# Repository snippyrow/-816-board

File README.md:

# Retro computer board!

A retro computer motherboard for the W65C816S CPU.
Dual-core expandable, 16mb extended memory, four expansion ports.

## *WHY* did I make this??
I have always loved building things with my hands, especially electronics things. I also love computers, and always to learn how they work. I believe that this is part of that hobby, building myself a computer system to play around with. I want to develop software, as well as expandable hardware. My end goal is to write a complete opertaing system for this build, and have it run DOOM!

# Basic Specifications
The primary core is a W65C816S microcontroller, with 32kb of SRAM. EEPROM Space is only accessible to the primary controller. Each core has its own cache, or SRAM chip. Located in the upper-half of the first page, each is 32kb. If the primary controller wants to access EEPROM, I.E. to copy data to another portion of memory, it only needs to access the lower-half. If the primary wants to access the secondary core cache, it uses the expanded memory space. There are two types of busses: core-only and global. The global bus is arbitrated between the two cores. The primary gets priority, then the secondary. In order for the first to access secondary, it must first disable the secondary core. This allows it to always be able to write. The primary core must not access the secondary core too often, as it must be disabled beforehand. If the secondary core needs to access the main bus, it queues to wait before the primary CPU does an internal cycle. At that moment it will take whatever is in the queue registers. This means that the secondary must not access the main memory too often. The secondary cache is only exposed to the global bus if the primary is using it for a transfer. 

The system is powerful enough to run a basic operating system, and provides options to expand into a workable computer system.

## Advanced
The system uses two cores, the W65C816S core. It is not a drop-in replacement for the W65C02S, and samples data during the falling edge of the PHI2. Each core starts in a 6502-emulation mode, and then transitions to the native '816 mode. Each core can access up to 16MB of memory and has 16-bit internal registers. The primary core contains 32kb of EEPROM space as well as 32kb of SRAM space. The secondary core is disabled at runtime, and must be re-enabled later. The low 65kb of the memory (2^16 bytes worth) are used to communicate and run simple programs. The 32kb space acts as a sort of cache system for each core, and they can communicate largely based on the upper shared memory. Beyond the low 65kb there are devices and expansion memory. The secondary core is unable to reach the primary core, though the primary core can access the secondary core by an expansion device. The first devices after the local memory are the expansion devices. Not only are the expansion ports physically on the board mapped here, but so is the control register for the secondary core, as well as the built-in serial port controller. 

While the primary core is not actively using the global/shared memory, the secondary core is free to do so. To upload a program or start a second process, the secondary core must first be disabled and reset. Then, the cache is accessed and the program is copied. The reset vector will point to some location in the cache, and it will be re-enabled. **Do not set the reset vector elsewhere.**
As stated previously, when the secondary core needs to access shared memory, whether that be an expansion device or general memory, it latches the address. If reading, it sets a control bit and waits for a NMIB. If writing, it sets the control but the other way and latches the write data. When the write is completed, I.E. once the primary is not active, a NMIB signal is sent signaling that the memory transaction was completed. The WAI (wait for interrupt) can be used. 
The system is based off an expanion-type model, where it encourages expansion devices to be built and used. Some examples could be a VGA card, sound card, or a keyboard/mouse system.

## Primary core operation
The core is initiated during a power-on reset phase. The secondary core is disabled during this time, and no secondary transactions are happening. The primary will disable the built-in serial port built in directly to the secondary, and can work without using the secondary core at all. It can use the global bus like the internal core bus.

## Secondary core operation
There are two bits that control the secondary core: ENABLE (0) and RESET (1). The ENABLE bit is used to turn the core on or of. It uses the RDY pin to do this. Enabling this also allows the queue to begin transferring data. The IRQB pin is used for the serial adapter, and the NMIB is used when an external read request has been completed. The RESET pin is used to control the RESB pin on the secondary, to reset it to a known state. It is recommended to disable the core using the ENABLE bit before changing data on the secondary cache. When the primary CPU goes into an internal cycle, it takes whatever value is in the address latches and will attempt a memory transaction. The only accessible area for the secondary is the expansion planes and the expanded memory lanes. The RWB bit will control whether it is reading or writing. Since this all takes a single cycle, timing does not matter. The secondary should not attempt frequent external writes due to speed limitations. The secondary only has access to up to half the expandable memory space, as the last bit is used internally for deciding whether it is reading the MMU register. A NMI also happens after a write, to tell the core that the write succeeded before overwriting the register again.

## Built-in serial adapter
The built-in serial adapter is wired directly to the secondary core IRQB pin. If it should be disabled, it can be done so by accessing the internal registers. It uses the R6551 chip. Does not include RS232. When reading data from the serial port, it must use the R6551 as an expansion device, located in the external memory lane. This is so that it can be externally controlled by the primary core. Attempt to read by accessing the global data bus, and wait for an interrupt on the NMIB pin. WAI can be used. The same goes for sending data.
The secondary should rely in the WAI instruction to manage external reads and writes, but could also be triggered by an IRQB signal from the serial adapter. Internal control should be programmed to prevent this. NMI has priority, after that an IRQB will be sent. The flow should be as follows: first an IRQB signal is sent, then an attempt to read the device will be followed by a NMIB signal. When a NMIB is sent during the IRQB routine, it will cause a nested interrupt to occur, allowing it to service properly. 

# Timing Control
Timing control is critical for this system. When PHI2 (the clock) goes from high to low, it indicated the start of a new cycle. VDA/VPA pins change about half-way during the PHI2 low period, and indicate whether the CPU is undergoing an internal cycle. Write and read cycles are all sampled on the falling edge. When VDA/VPA update shortly after the falling edge, the primary core is disconnected from the global bus, and it prepares to do a transaction by updating the address that was latched before. write data is also placed onto the data bus if necessary. On the next falling edge, data is written or data is read. If read, it then sends a NMI to tell the core that it read the data. From there it will read the data back from a specific register. When using it to read, it does not exactly read directly from the memory devices. Instead, it reads from a memory management unit that waits for the primary core to open. The secondary can read the MMU register, located in the upper half of the expandable memory space (bit 23). In order to disconnect the primary, BE is set high, disconnecting the data and address busses. Afterwards, the latches are turned on. 
Immediately after the bank address is pushed to the data bus, all read data begins to enter through either the cache space or the shared memory space. RDY is toggled by the control of the first bit in the control register, and is only sampled and updated on the following falling edge of the PHI2.

## Examples
If the primary wants to upload something to the secondary, I.E. change the task, it will first disable the core and push it into a reset. This prevent erroneous memory accesses. Then, with the cache mapped as an expansion memory device, begins accessing. The primary is **blocked** from accessing the secondary cache if the core is active. The only way for the two to communicate is through the shared global memory tables. After it is completed, re-enable the secondary.

# Expansion Ports
The machine contains four expansion ports, wired directly to the primary. Two of the slots are larger, and each one of the two is either wired to IRQB or NMIB. The other two are simply expansion devices. The larger ones have A0-A3, and the smaller ones have A0-A1 as register addresses. The shared memory on the global bus is beyond the 65K from the two cores.
The controller for the secondary, the controller for the serial port, and just about everything else is connected in through the expansion device encoder to save on space.

# Physical Board Explaination
### Primary Core
The primary core uses the W65C816S, with a 24-bit address bus and an 8-bit data bus. The highest byte of the address bus (A16-A23) is pushed onto the data bus during the low phase of PHI2, and is latched at the rising edge of the clock. The address bus comes stable around the same time. During these times, all the chips may stabilize into selecting the correct hardware for the write. Each core has a 74HC373 and a 74HC245 to moderate the data bus and the banked address busses. The BE pin will set the data bus, address bus and RWB pins to high-Z. The banked address byte is fed into a chip that detects if it is anything >0x00. This means that an external cycle is being attempted. If not, the selection uses A15 to select from either RAM or ROM to read/write from. In an external cycle, the primary is shut off from the rest of the device. During an external cycle, the full address is passed to the global address bus, and the data is either passed through from the data bus directly or read in through an octal buffer. The RWB pin is multiplexed along with the secondary.
The expansion slots are wired directly into the primary core NMIB/IRQB pins, and are pulled high on the board. 

### Secondary Core
The secondary core has much the same setup as the primary core, but has some key differences. It can work independently of the primary through its own cache, but lacks an EEPROM space. In order to perform an external read/write, when it detects an external memory transaction it always writes to a large set of registers. These registers latch A0-A22, as well as whether it wants to read or write. It may not be necessary for it to use the full 16MB address space. The secondary cache lies outside of the range that the secondary can reach. When it is latched, it also sets a D-flipflop into a HIGH state. The state of the first flip-flop is transferred over to the external memory device selector, which can choose which device to enable. It is only active during either an external cycle made by the primary or the secondary waiting to write/read data. Now that the devices have a stable address, when an external cycle happens, it sets the second flip-flop into a HIGH state. This will immediately reset both back to LOW, but sends a NMI to the secondary processor.
During an external cycle, the secondary processor latches are always pushed out to the global bus, as well as any data. If no core is desiring to read from the global data bus, then it may go floating. If the secondary desired to write previously, that old data would be pushed, otherwise nothing holds on to the data bus. Therefore the global data bus is always pulled LOW.
A15 is always pulled LOW, and in order to *read* data coming from the global busses, any address from 0x0000-0x7FFF will work. It simply takes the place of the EEPROM space. On the secondary the cache is in the upper half rather than lower.
The secondary processor has two control bits, ENABLE and RESET. ENABLE will control the processor state, pausing it and disabling the address/data busses. The RESET bit will cause it to reset back to a known state. The secondary processor will have all of its data and address busses disabled during this time. The cache can be accessed by the primary core processor during this time, while it is disabled. *It cannot access while running.* While the address and data busses are in a High-Z state, the cache can be selected as an expansion device, and the address/data/RWB for the primary processor are pushed in. The secondary local data bus are always pulled LOW. The secondary address bus is always matches the primary address bus while not enabled, as a way to drive it.

#### Serial adapter
As mentioned earlier, the serial adapter is wired directly to the secondary core, and works as any other expansion device would. The secondary should either disable the adapter or mask interrupts if it were to be doing something other than serial work.

#### Memory selector
The memory selector works entirely off the global address busses for selection, choosing serial devices or memory expansion cards. Devices are only selected if either there is an external cycle or the secondary is waiting to write data. 

# Datasheets
https://www.westerndesigncenter.com/wdc/documentation/w65c816s.pdf

# BOM
| Item               | Quantity | Price (USD) |
|--------------------|----------|-------------|
| JLCPCB 180x140mm | 5 | $25.15 |
| 10K Resistor       | 10       | $1.85       |
| SN74HC373N Latch   | 10       | $9.77       |
| W65C816S6PG-14 MPU | 2        | $24.20      |
| L78L33 Regulator   | 5        | $1.40       |
| 10uF Capacitor     | 5        | $1.15       |
| LED (Red)          | 10       | $2.60       |
| SN74HC04N Inverter | 5        | $6.55       |
| SN74HC21N Gate     | 4        | $2.60       |
| Tactile Switch     | 5        | $1.50       |
| SN74HC245N Transceiver | 10    | $6.22       |
| AT28C256 EEPROM    | 1        | $11.62      |
| 150Ω Resistor      | 4        | $1.44       |
| AS6C62256 SRAM     | 2        | $9.50       |
| 1MΩ Resistor       | 4        | $1.44       |
| SN74HC138N Decoder | 5        | $5.50       |
| 1N914 Diode        | 5        | $0.50       |
| SN74HC10N Gate     | 4        | $2.52       |
| 10kΩ Resistor      | 20       | $0.30       |
| 1kΩ Resistor       | 10       | $0.27       |
| SN74HC32N Gate     | 4        | $2.20       |
| SN74HC688N Comparator | 6     | $8.52       |
| 4.7kΩ Resistor     | 10       | $0.47       |
| SN74HC126N Buffer  | 4        | $2.64       |
| SN74HC00N Gate     | 5        | $3.00       |
| 2N3904 Transistor  | 10       | $0.77       |
| 30pF Capacitor     | 10       | $1.18       |
| 0.1uF Capacitor    | 100      | $4.00       |
| 1MHz Oscillator    | 2        | $6.90       |
| SN74HC08N Gate     | 4        | $2.40       |
| SN74HC74N Flip Flop| 4        | $3.60       |
| 20-pin Socket      | 24       | $3.10       |
| 16-pin Socket      | 20       | $2.42       |
| 14-pin Socket      | 20       | $2.20       |
| 28-pin Socket      | 6        | $3.84       |
| 40-pin Socket      | 4        | $3.68       |

**Total: $167.00**

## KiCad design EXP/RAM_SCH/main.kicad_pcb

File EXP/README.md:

# Custom computer expansion cards!

A collection of expansion cards I plan to build for my custom dual-core W65C816S motherboard. Two examples include: a basic text-based graphics card, and some 2MB RAM modules.

## Why Did I Build These?
A computer without a graphical display, or RAM sticks is pretty useless. You can run some basic algorithms, but that's about it. These pieces of customized hardware will *drastically* improve that this build can do. For more information, please see the parent directory for the main build.

# About
# If you want to see specifics for each expansion card I plan to build, see the directories listed here in this folder.

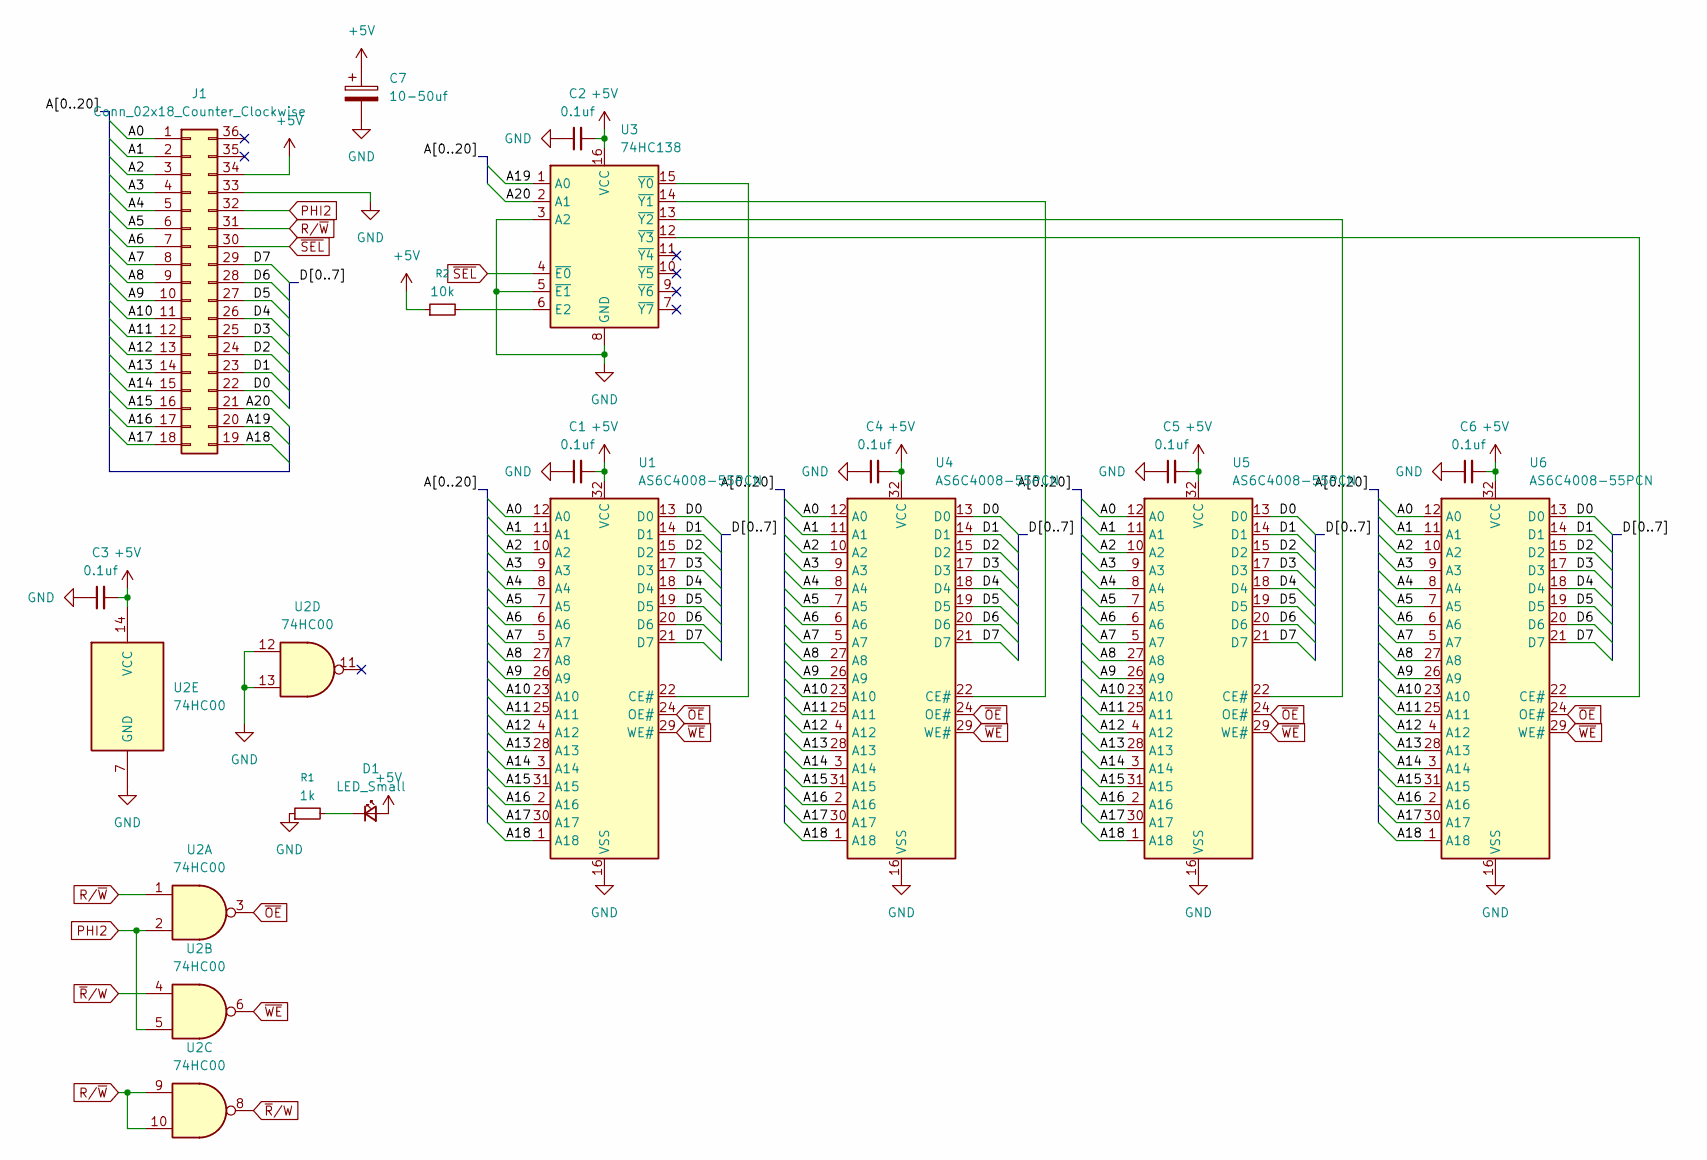
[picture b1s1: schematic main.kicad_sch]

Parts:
C1, C2, C3, C4, C5, C6: 0.1uf; C_Disc_D5.0mm_W2.5mm_P5.00mm
C7: 10-50uf; CP_Radial_D6.3mm_P2.50mm
D1: LED_Small; LED_D3.0mm
J1: Conn_02x18_Counter_Clockwise; AliExpress_36Edge
R1: 1k; R_Axial_DIN0204_L3.6mm_D1.6mm_P5.08mm_Horizontal
R2: 10k; R_Axial_DIN0204_L3.6mm_D1.6mm_P5.08mm_Horizontal
U1, U4, U5, U6: AS6C4008-55PCN; DIP-32_W15.24mm
U2: 74HC00; DIP-14_W7.62mm_Socket
U3: 74HC138; DIP-16_W7.62mm_Socket

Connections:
+5V: C1.2, C2.2, C3.2, C4.2, C5.2, C6.2, C7.1, D1.2 (A), J1.34, R2.1, U1.32 (VCC), U2.14 (VCC), U3.16 (VCC), U4.32 (VCC), U5.32 (VCC), U6.32 (VCC)
/A0: J1.1, U1.12 (A0), U4.12 (A0), U5.12 (A0), U6.12 (A0)
/A1: J1.2, U1.11 (A1), U4.11 (A1), U5.11 (A1), U6.11 (A1)
/A2: J1.3, U1.10 (A2), U4.10 (A2), U5.10 (A2), U6.10 (A2)
/A3: J1.4, U1.9 (A3), U4.9 (A3), U5.9 (A3), U6.9 (A3)
/A4: J1.5, U1.8 (A4), U4.8 (A4), U5.8 (A4), U6.8 (A4)
/A5: J1.6, U1.7 (A5), U4.7 (A5), U5.7 (A5), U6.7 (A5)
/A6: J1.7, U1.6 (A6), U4.6 (A6), U5.6 (A6), U6.6 (A6)
/A7: J1.8, U1.5 (A7), U4.5 (A7), U5.5 (A7), U6.5 (A7)
/A8: J1.9, U1.27 (A8), U4.27 (A8), U5.27 (A8), U6.27 (A8)
/A9: J1.10, U1.26 (A9), U4.26 (A9), U5.26 (A9), U6.26 (A9)
/A10: J1.11, U1.23 (A10), U4.23 (A10), U5.23 (A10), U6.23 (A10)
/A11: J1.12, U1.25 (A11), U4.25 (A11), U5.25 (A11), U6.25 (A11)
/A12: J1.13, U1.4 (A12), U4.4 (A12), U5.4 (A12), U6.4 (A12)
/A13: J1.14, U1.28 (A13), U4.28 (A13), U5.28 (A13), U6.28 (A13)
/A14: J1.15, U1.3 (A14), U4.3 (A14), U5.3 (A14), U6.3 (A14)
/A15: J1.16, U1.31 (A15), U4.31 (A15), U5.31 (A15), U6.31 (A15)
/A16: J1.17, U1.2 (A16), U4.2 (A16), U5.2 (A16), U6.2 (A16)
/A17: J1.18, U1.30 (A17), U4.30 (A17), U5.30 (A17), U6.30 (A17)
/A18: J1.19, U1.1 (A18), U4.1 (A18), U5.1 (A18), U6.1 (A18)
/A19: J1.20, U3.1 (A0)
/A20: J1.21, U3.2 (A1)
/D0: J1.22, U1.13 (D0), U4.13 (D0), U5.13 (D0), U6.13 (D0)
/D1: J1.23, U1.14 (D1), U4.14 (D1), U5.14 (D1), U6.14 (D1)
/D2: J1.24, U1.15 (D2), U4.15 (D2), U5.15 (D2), U6.15 (D2)
/D3: J1.25, U1.17 (D3), U4.17 (D3), U5.17 (D3), U6.17 (D3)
/D4: J1.26, U1.18 (D4), U4.18 (D4), U5.18 (D4), U6.18 (D4)
/D5: J1.27, U1.19 (D5), U4.19 (D5), U5.19 (D5), U6.19 (D5)
/D6: J1.28, U1.20 (D6), U4.20 (D6), U5.20 (D6), U6.20 (D6)
/D7: J1.29, U1.21 (D7), U4.21 (D7), U5.21 (D7), U6.21 (D7)
GND: C1.1, C2.1, C3.1, C4.1, C5.1, C6.1, C7.2, J1.33, R1.1, U1.16 (VSS), U2.7 (GND), U2.12, U2.13, U3.3 (A2), U3.5 (~E1), U3.8 (GND), U4.16 (VSS), U5.16 (VSS), U6.16 (VSS)
unnamed: D1.1 (K), R1.2
unnamed: U1.22 (CE#), U3.15 (~Y0)
unnamed: R2.2, U3.6 (E2)
unnamed: U3.14 (~Y1), U4.22 (CE#)
unnamed: U3.13 (~Y2), U5.22 (CE#)
unnamed: U3.12 (~Y3), U6.22 (CE#)
PHI2: J1.32, U2.2, U2.5
R/~W: J1.31, U2.1, U2.9, U2.10
~OE: U1.24 (OE#), U2.3, U4.24 (OE#), U5.24 (OE#), U6.24 (OE#)
~R/W: U2.4, U2.8
~SEL: J1.30, U3.4 (~E0)
~WE: U1.29 (WE#), U2.6, U4.29 (WE#), U5.29 (WE#), U6.29 (WE#)

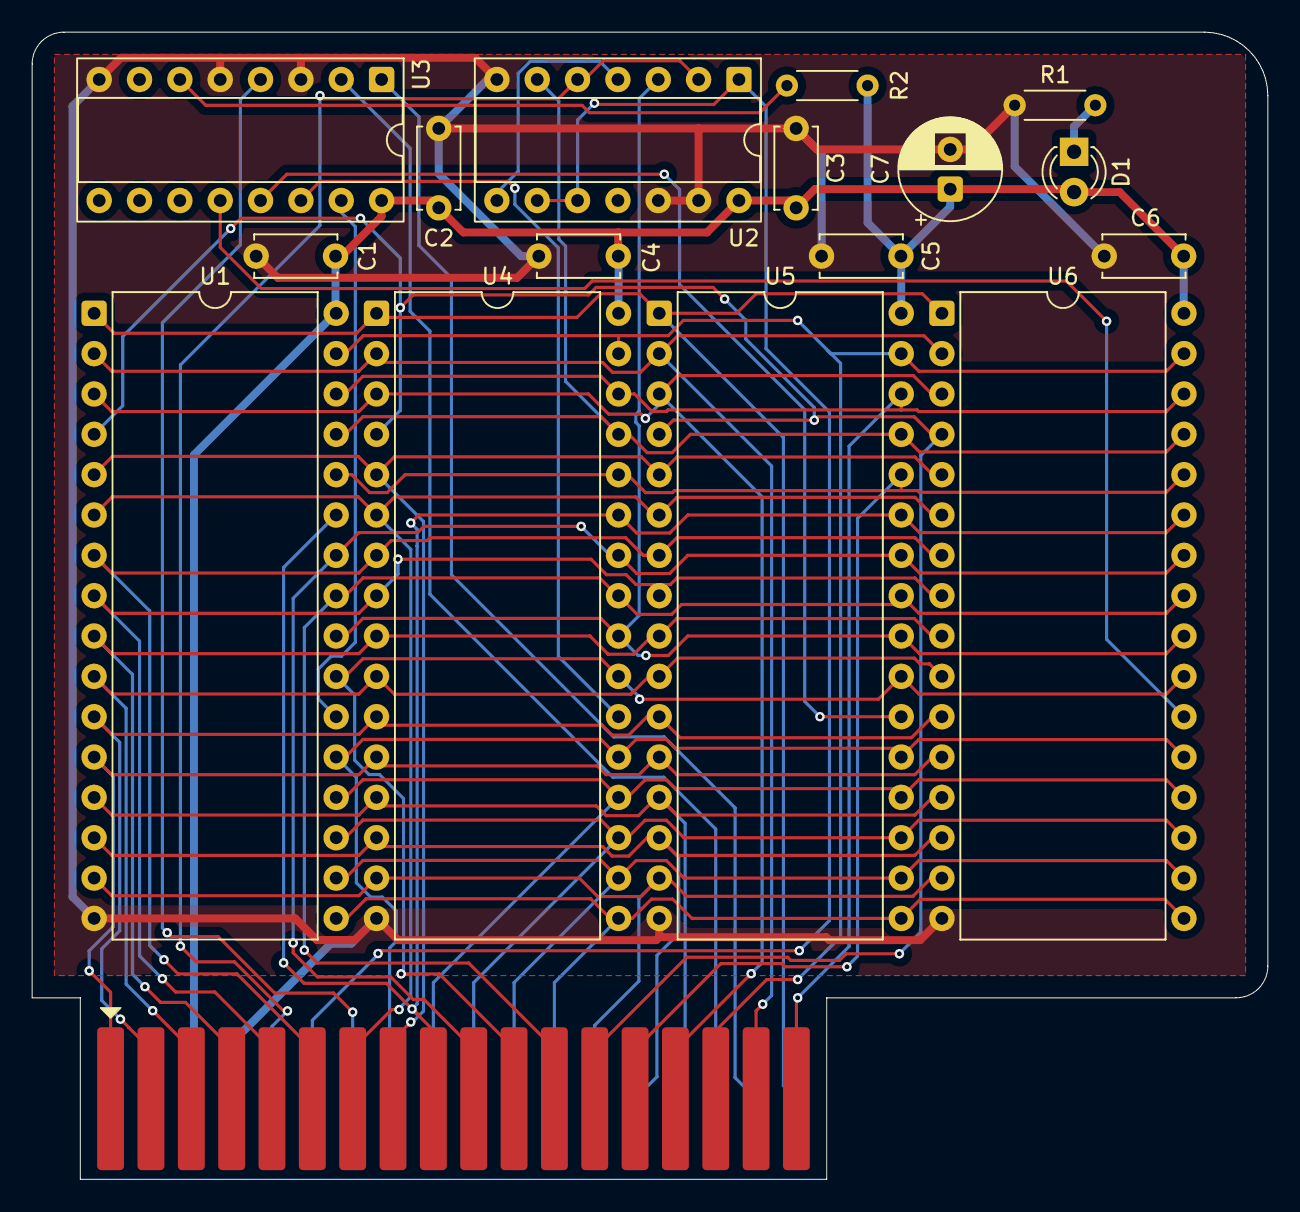
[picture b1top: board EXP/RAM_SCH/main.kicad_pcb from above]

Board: 2 copper layers, 77.8 x 72.2 mm, 17 parts (0 on the bottom side), 43 nets.

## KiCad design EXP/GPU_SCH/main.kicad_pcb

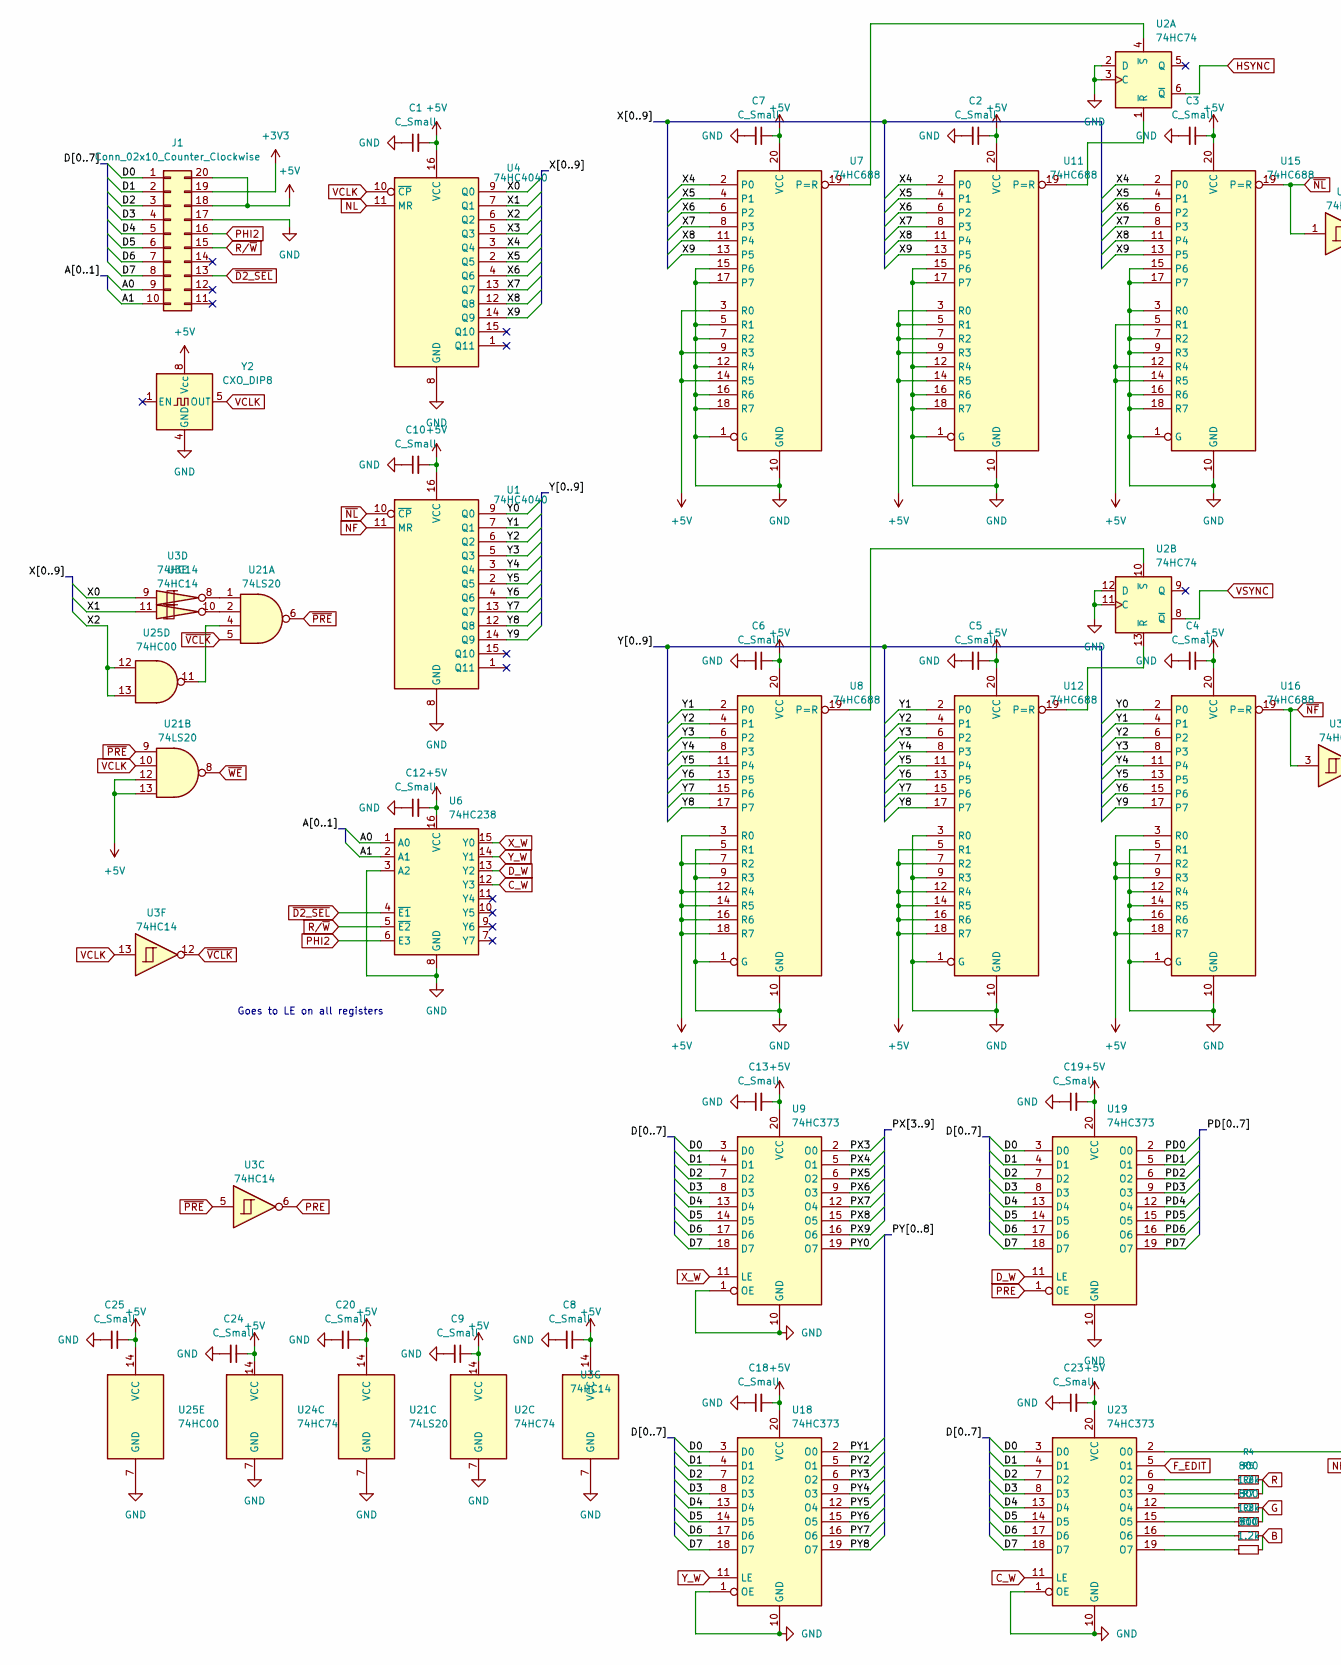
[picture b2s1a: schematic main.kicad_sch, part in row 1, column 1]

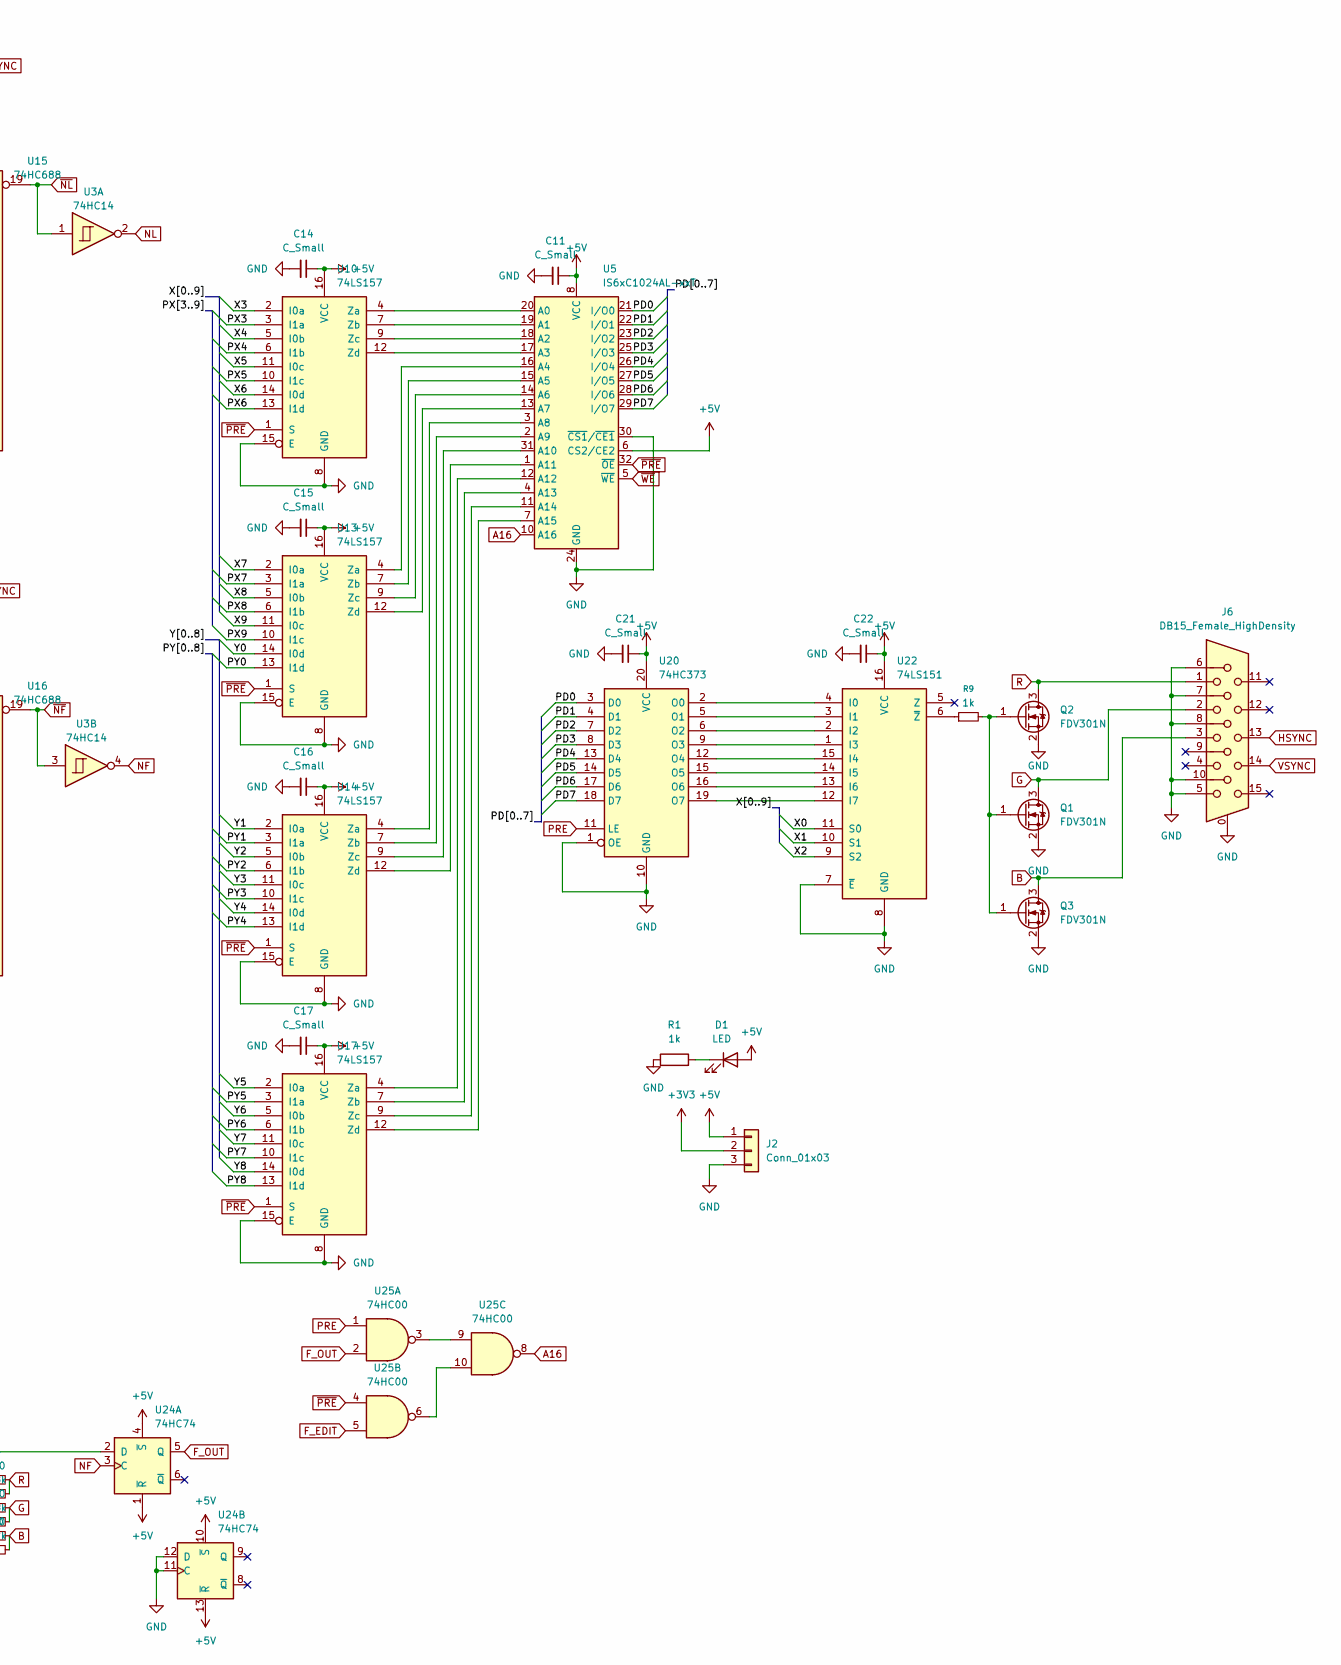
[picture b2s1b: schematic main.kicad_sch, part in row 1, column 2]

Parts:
C1, C2, C3, C4, C5, C6, C7, C8, C9, C10, C11, C12, C13, C14, C15, C16, C17, C18, C19, C20, C21, C22, C23, C24, C25: C_Small; C_Disc_D3.0mm_W2.0mm_P2.50mm
D1: LED; LED_D3.0mm
J1: Conn_02x10_Counter_Clockwise; AliExpress_20Edge
J2: Conn_01x03; PinSocket_1x03_P2.54mm_Vertical
J6: DB15_Female_HighDensity; DSUB-15-HD_Socket_Horizontal_P2.29x1.90mm_EdgePinOffset3.03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
Q1, Q2, Q3: FDV301N; SOT-23-3
R1, R9: 1k; R_Axial_DIN0204_L3.6mm_D1.6mm_P5.08mm_Horizontal
R4, R6, R8: 800; R_Axial_DIN0204_L3.6mm_D1.6mm_P5.08mm_Horizontal
R5, R7, R10: 1.2k; R_Axial_DIN0204_L3.6mm_D1.6mm_P5.08mm_Horizontal
U1, U4: 74HC4040; DIP-16_W7.62mm_Socket
U2, U24: 74HC74; DIP-14_W7.62mm_Socket
U3: 74HC14; DIP-14_W7.62mm_Socket
U5: IS6xC1024AL-xxT; TSOP-I-32_18.4x8mm_P0.5mm
U6: 74HC238; DIP-16_W7.62mm_Socket
U7, U8, U11, U12, U15, U16: 74HC688; DIP-20_W7.62mm_Socket
U9, U18, U19, U20, U23: 74HC373; DIP-20_W7.62mm_Socket
U10, U13, U14, U17: 74LS157; DIP-16_W7.62mm_Socket
U21: 74LS20; DIP-14_W7.62mm_Socket
U22: 74LS151; DIP-16_W7.62mm_Socket
U25: 74HC00; DIP-14_W7.62mm_Socket
Y2: CXO_DIP8; Oscillator_DIP-8

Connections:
+3V3: J1.19, J2.2
+5V: C1.2, C2.1, C3.1, C4.1, C5.1, C6.1, C7.1, C8.1, C9.1, C10.2, C11.1, C12.2, C13.2, C14.1, C15.1, C16.1, C17.1, C18.2, C19.2, C20.1, C21.1, C22.1, C23.2, C24.1, C25.1, D1.2 (A), J1.18, J1.20, J2.1, U1.16 (VCC), U2.14 (VCC), U3.14 (VCC), U4.16 (VCC), U5.6 (CS2/CE2), U5.8 (VCC), U6.16 (VCC), U7.3 (R0), U7.9 (R3), U7.14 (R5), U7.20 (VCC), U8.3 (R0), U8.7 (R2), U8.12 (R4), U8.14 (R5), U8.16 (R6), U8.18 (R7), U8.20 (VCC), U9.20 (VCC), U10.16 (VCC), U11.3 (R0), U11.5 (R1), U11.7 (R2), U11.9 (R3), U11.14 (R5), U11.20 (VCC), U12.5 (R1), U12.7 (R2), U12.12 (R4), U12.14 (R5), U12.16 (R6), U12.18 (R7), U12.20 (VCC), U13.16 (VCC), U14.16 (VCC), U15.5 (R1), U15.12 (R4), U15.14 (R5), U15.20 (VCC), U16.3 (R0), U16.7 (R2), U16.9 (R3), U16.18 (R7), U16.20 (VCC), U17.16 (VCC), U18.20 (VCC), U19.20 (VCC), U20.20 (VCC), U21.12, U21.13, U21.14 (VCC), U22.16 (VCC), U23.20 (VCC), U24.1 (~R), U24.4 (~S), U24.10 (~S), U24.13 (~R), U24.14 (VCC), U25.14 (VCC), Y2.8 (Vcc)
/A0: J1.9, U6.1 (A0)
/A1: J1.10, U6.2 (A1)
/D0: J1.1, U9.3 (D0), U18.3 (D0), U19.3 (D0), U23.3 (D0)
/D1: J1.2, U9.4 (D1), U18.4 (D1), U19.4 (D1), U23.4 (D1)
/D2: J1.3, U9.7 (D2), U18.7 (D2), U19.7 (D2), U23.7 (D2)
/D3: J1.4, U9.8 (D3), U18.8 (D3), U19.8 (D3), U23.8 (D3)
/D4: J1.5, U9.13 (D4), U18.13 (D4), U19.13 (D4), U23.13 (D4)
/D5: J1.6, U9.14 (D5), U18.14 (D5), U19.14 (D5), U23.14 (D5)
/D6: J1.7, U9.17 (D6), U18.17 (D6), U19.17 (D6), U23.17 (D6)
/D7: J1.8, U9.18 (D7), U18.18 (D7), U19.18 (D7), U23.18 (D7)
/PD0: U5.21 (I/O0), U19.2 (O0), U20.3 (D0)
/PD1: U5.22 (I/O1), U19.5 (O1), U20.4 (D1)
/PD2: U5.23 (I/O2), U19.6 (O2), U20.7 (D2)
/PD3: U5.25 (I/O3), U19.9 (O3), U20.8 (D3)
/PD4: U5.26 (I/O4), U19.12 (O4), U20.13 (D4)
/PD5: U5.27 (I/O5), U19.15 (O5), U20.14 (D5)
/PD6: U5.28 (I/O6), U19.16 (O6), U20.17 (D6)
/PD7: U5.29 (I/O7), U19.19 (O7), U20.18 (D7)
/PX3: U9.2 (O0), U10.3 (I1a)
/PX4: U9.5 (O1), U10.6 (I1b)
/PX5: U9.6 (O2), U10.10 (I1c)
/PX6: U9.9 (O3), U10.13 (I1d)
/PX7: U9.12 (O4), U13.3 (I1a)
/PX8: U9.15 (O5), U13.6 (I1b)
/PX9: U9.16 (O6), U13.10 (I1c)
/PY0: U9.19 (O7), U13.13 (I1d)
/PY1: U14.3 (I1a), U18.2 (O0)
/PY2: U14.6 (I1b), U18.5 (O1)
/PY3: U14.10 (I1c), U18.6 (O2)
/PY4: U14.13 (I1d), U18.9 (O3)
/PY5: U17.3 (I1a), U18.12 (O4)
/PY6: U17.6 (I1b), U18.15 (O5)
/PY7: U17.10 (I1c), U18.16 (O6)
/PY8: U17.13 (I1d), U18.19 (O7)
/X0: U3.9, U4.9 (Q0), U22.11 (S0)
/X1: U3.11, U4.7 (Q1), U22.10 (S1)
/X2: U4.6 (Q2), U22.9 (S2), U25.12, U25.13
/X3: U4.5 (Q3), U10.2 (I0a)
/X4: U4.3 (Q4), U7.2 (P0), U10.5 (I0b), U11.2 (P0), U15.2 (P0)
/X5: U4.2 (Q5), U7.4 (P1), U10.11 (I0c), U11.4 (P1), U15.4 (P1)
/X6: U4.4 (Q6), U7.6 (P2), U10.14 (I0d), U11.6 (P2), U15.6 (P2)
/X7: U4.13 (Q7), U7.8 (P3), U11.8 (P3), U13.2 (I0a), U15.8 (P3)
/X8: U4.12 (Q8), U7.11 (P4), U11.11 (P4), U13.5 (I0b), U15.11 (P4)
/X9: U4.14 (Q9), U7.13 (P5), U11.13 (P5), U13.11 (I0c), U15.13 (P5)
/Y0: U1.9 (Q0), U13.14 (I0d), U16.2 (P0)
/Y1: U1.7 (Q1), U8.2 (P0), U12.2 (P0), U14.2 (I0a), U16.4 (P1)
/Y2: U1.6 (Q2), U8.4 (P1), U12.4 (P1), U14.5 (I0b), U16.6 (P2)
/Y3: U1.5 (Q3), U8.6 (P2), U12.6 (P2), U14.11 (I0c), U16.8 (P3)
/Y4: U1.3 (Q4), U8.8 (P3), U12.8 (P3), U14.14 (I0d), U16.11 (P4)
/Y5: U1.2 (Q5), U8.11 (P4), U12.11 (P4), U16.13 (P5), U17.2 (I0a)
/Y6: U1.4 (Q6), U8.13 (P5), U12.13 (P5), U16.15 (P6), U17.5 (I0b)
/Y7: U1.13 (Q7), U8.15 (P6), U12.15 (P6), U17.11 (I0c)
/Y8: U1.12 (Q8), U8.17 (P7), U12.17 (P7), U17.14 (I0d)
/Y9: U1.14 (Q9), U16.17 (P7)
A16: U5.10 (A16), U25.8
B: J6.3, Q3.3 (D), R8.2, R10.2
C_W: U6.12 (Y3), U23.11 (LE)
D_W: U6.13 (Y2), U19.11 (LE)
F_EDIT: U23.5 (O1), U25.5
F_OUT: U24.5 (Q), U25.2
G: J6.2, Q1.3 (D), R6.2, R7.2
GND: C1.1, C2.2, C3.2, C4.2, C5.2, C6.2, C7.2, C8.2, C9.2, C10.1, C11.2, C12.1, C13.1, C14.2, C15.2, C16.2, C17.2, C18.1, C19.1, C20.2, C21.2, C22.2, C23.1, C24.2, C25.2, J1.17, J2.3, J6.0, J6.5, J6.6, J6.7, J6.8, J6.10, Q1.2 (S), Q2.2 (S), Q3.2 (S), R1.1, U1.8 (GND), U2.2 (D), U2.3 (C), U2.7 (GND), U2.11 (C), U2.12 (D), U3.7 (GND), U4.8 (GND), U5.24 (GND), U5.30 (~CS1/~CE1), U6.3 (A2), U6.8 (GND), U7.1 (G), U7.5 (R1), U7.7 (R2), U7.10 (GND), U7.12 (R4), U7.15 (P6), U7.16 (R6), U7.17 (P7), U7.18 (R7), U8.1 (G), U8.5 (R1), U8.9 (R3), U8.10 (GND), U9.1 (OE), U9.10 (GND), U10.8 (GND), U10.15 (E), U11.1 (G), U11.10 (GND), U11.12 (R4), U11.15 (P6), U11.16 (R6), U11.17 (P7), U11.18 (R7), U12.1 (G), U12.3 (R0), U12.9 (R3), U12.10 (GND), U13.8 (GND), U13.15 (E), U14.8 (GND), U14.15 (E), U15.1 (G), U15.3 (R0), U15.7 (R2), U15.9 (R3), U15.10 (GND), U15.15 (P6), U15.16 (R6), U15.17 (P7), U15.18 (R7), U16.1 (G), U16.5 (R1), U16.10 (GND), U16.12 (R4), U16.14 (R5), U16.16 (R6), U17.8 (GND), U17.15 (E), U18.1 (OE), U18.10 (GND), U19.10 (GND), U20.1 (OE), U20.10 (GND), U21.7 (GND), U22.7 (~E), U22.8 (GND), U23.1 (OE), U23.10 (GND), U24.7 (GND), U24.11 (C), U24.12 (D), U25.7 (GND), Y2.4 (GND)
HSYNC: J6.13, U2.6 (~Q)
NF: U1.11 (MR), U3.4, U24.3 (C)
NL: U3.2, U4.11 (MR)
unnamed: D1.1 (K), R1.2
unnamed: Q1.1 (G), Q2.1 (G), Q3.1 (G), R9.2
unnamed: U2.4 (~S), U7.19 (P=R)
unnamed: U2.10 (~S), U8.19 (P=R)
unnamed: U5.20 (A0), U10.4 (Za)
unnamed: U5.19 (A1), U10.7 (Zb)
unnamed: U5.18 (A2), U10.9 (Zc)
unnamed: U5.17 (A3), U10.12 (Zd)
unnamed: U2.1 (~R), U11.19 (P=R)
unnamed: U2.13 (~R), U12.19 (P=R)
unnamed: U5.16 (A4), U13.4 (Za)
unnamed: U5.15 (A5), U13.7 (Zb)
unnamed: U5.14 (A6), U13.9 (Zc)
unnamed: U5.13 (A7), U13.12 (Zd)
unnamed: U5.3 (A8), U14.4 (Za)
unnamed: U5.2 (A9), U14.7 (Zb)
unnamed: U5.31 (A10), U14.9 (Zc)
unnamed: U5.1 (A11), U14.12 (Zd)
unnamed: U5.12 (A12), U17.4 (Za)
unnamed: U5.4 (A13), U17.7 (Zb)
unnamed: U5.11 (A14), U17.9 (Zc)
unnamed: U5.7 (A15), U17.12 (Zd)
unnamed: U20.2 (O0), U22.4 (I0)
unnamed: U20.5 (O1), U22.3 (I1)
unnamed: U20.6 (O2), U22.2 (I2)
unnamed: U20.9 (O3), U22.1 (I3)
unnamed: U20.12 (O4), U22.15 (I4)
unnamed: U20.15 (O5), U22.14 (I5)
unnamed: U20.16 (O6), U22.13 (I6)
unnamed: U20.19 (O7), U22.12 (I7)
unnamed: U3.8, U21.1
unnamed: U3.10, U21.2
unnamed: U21.4, U25.11
unnamed: R9.1, U22.6 (~Z)
unnamed: U23.2 (O0), U24.2 (D)
unnamed: R4.1, U23.6 (O2)
unnamed: R5.1, U23.9 (O3)
unnamed: R6.1, U23.12 (O4)
unnamed: R7.1, U23.15 (O5)
unnamed: R8.1, U23.16 (O6)
unnamed: R10.1, U23.19 (O7)
unnamed: U25.3, U25.9
unnamed: U25.6, U25.10
PHI2: J1.16, U6.6 (E3)
PRE: U3.6, U19.1 (OE), U20.11 (LE), U25.1
R: J6.1, Q2.3 (D), R4.2, R5.2
R/~W: J1.15, U6.5 (~E2)
VCLK: U3.13, U4.10 (~CP), U21.10, Y2.5 (OUT)
VSYNC: J6.14, U2.8 (~Q)
X_W: U6.15 (Y0), U9.11 (LE)
Y_W: U6.14 (Y1), U18.11 (LE)
~D2_SEL: J1.13, U6.4 (~E1)
~NF: U3.3, U16.19 (P=R)
~NL: U1.10 (~CP), U3.1, U15.19 (P=R)
~PRE: U3.5, U5.32 (~OE), U10.1 (S), U13.1 (S), U14.1 (S), U17.1 (S), U21.6, U21.9, U25.4
~VCLK: U3.12, U21.5
~WE: U5.5 (~WE), U21.8

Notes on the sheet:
Goes to LE on all registers

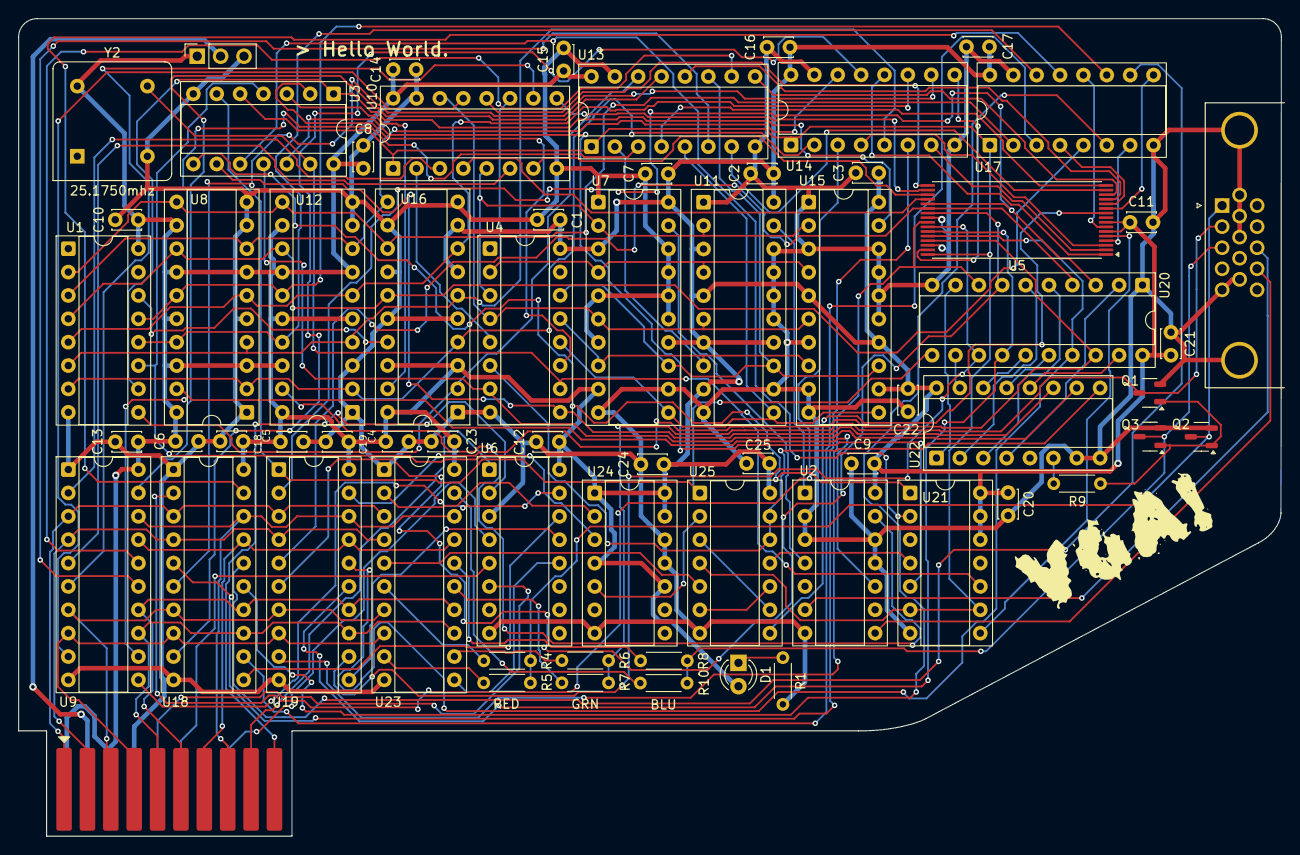
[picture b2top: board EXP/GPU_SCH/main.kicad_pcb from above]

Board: 2 copper layers, 137.2 x 88.8 mm, 66 parts (0 on the bottom side), 124 nets.
